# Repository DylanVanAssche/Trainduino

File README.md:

ReadMe Trainduino
=================

Trainduino is a project that combines the power of the Arduino with the beautifull modeltrains. 
The electronics that are avaibale in the modeltrain world are overpriced for the limited functions they have, 
so this is your alternative!

RandomLEDController
-------------------

Controls a day/night process on my modelroad. It works with a cylcus of 24 minutes. 
Every minute counts the Arduino as one 'hour'.After the whole cyclus, the Arduino resets the timer.
The RandomLEDController can control 14 LED's in houses and has also 1 output for the streetlights.

RGBLEDController
----------------

Does the same as the RandomLEDController but this time it controls a RGB LEDstrip and a white LEDstrip to simulate a 
completely day/night. It runs synchrone with the RandomLEDController because it use the same timer system.

DCCSwitchController
-------------------

DCC accessory decoder with some extra nice functions. You can control 2 switches and 1 brake module.
There are also 4 outputs for a signal. The 3 LED's on the board show the status of the incomming commands.

S88Wireless
-----------

The S88Wireless system give you the possibilities to use your cheap S88 bus over a wireless connection. 
It's perfectly for a railroad track that has to be flexible and portable since you don't need the 6pin ribbon cable all around your layout!

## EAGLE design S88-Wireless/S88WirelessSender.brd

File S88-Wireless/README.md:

S88Wireless
-----------

The S88Wireless system is an Arduino based S88 feedback unit that transfers his data over a Wireless 2.4 Ghz connection.
The radio that we used for the S88Wireless is a cheap NRF24L01+ unit.

The BASE sketch collects all the information from the slave with a polling request and sends out the data on the S88 bus of your command station. The BASE sketch also monitors the data and checks if the slaves are alive. If not, the BASE sketch will trigger an emergency stop on your command station by using the short circuit detection from the DCC booster bus.

The SLAVE sketch monitors 8 pins and reports the status back to the base when the slave have been polled by the base.

The EAGLE PCB's are also available in this repository.

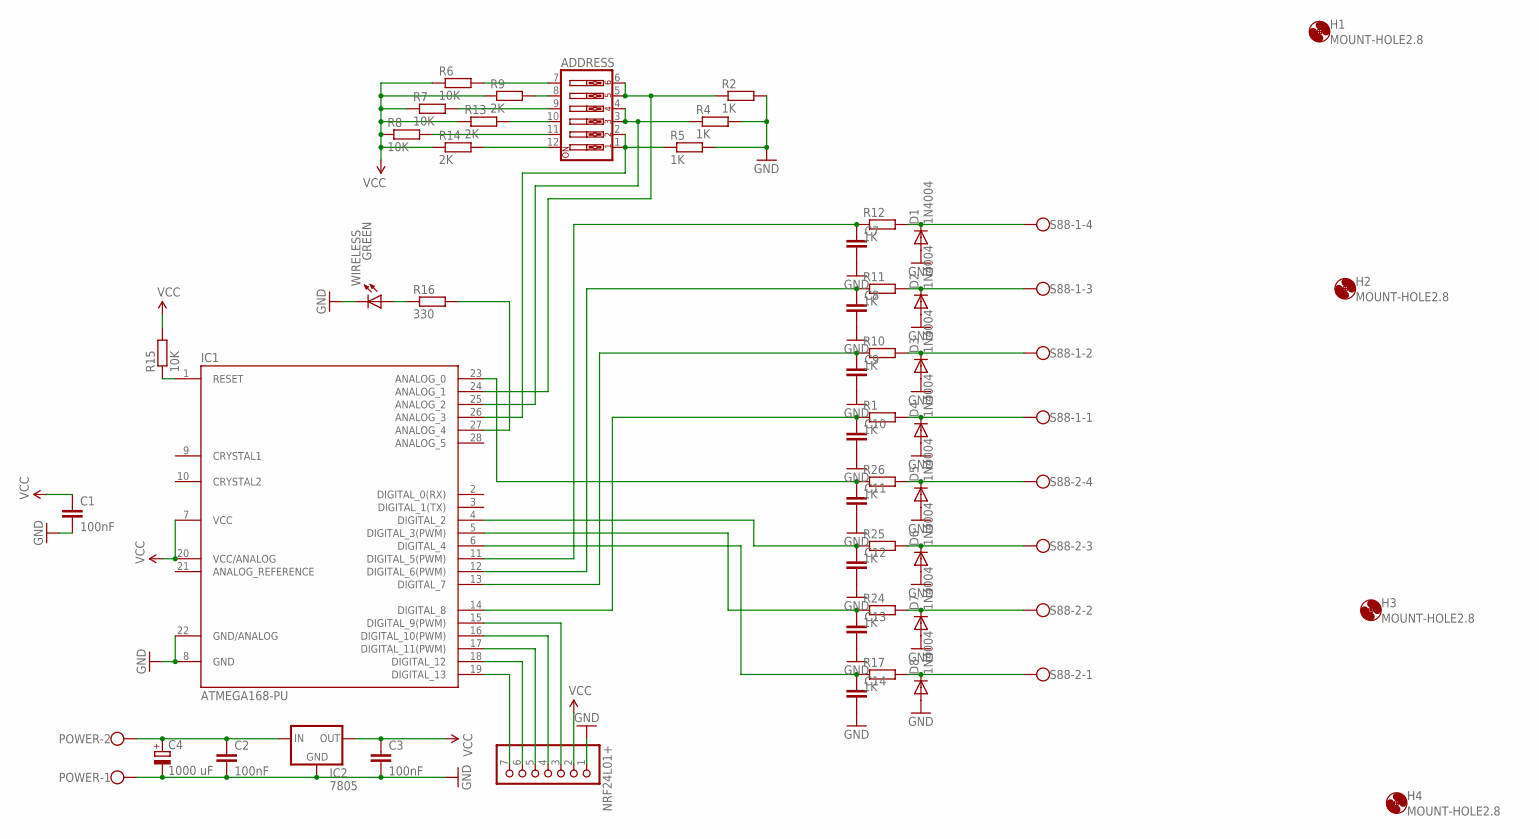
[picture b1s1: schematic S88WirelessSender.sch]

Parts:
ADDRESS: SW_DIP-6; EDG-06
C1, C2, C3: 100nF; C025-030X050
C4: 1000 uF; E5-13
C7, C8, C9, C10, C11, C12, C13, C14: C-EU025-024X044; C025-024X044
D1, D2, D3, D4, D5, D6, D7, D8: 1N4004; DO41-10
H1, H2, H3, H4: MOUNT-HOLE2.8; 2,8
IC1: ATMEGA168-PU; DIL28-3
IC2: 7805; 78XXS
NRF24L01+: PINHD-1X7; 1X07
POWER: W237-102
R1, R2, R4, R5, R10, R11, R12, R17, R24, R25, R26: 1K; 0204/7
R6, R7, R8, R15: 10K; 0204V
R9, R13, R14: 2K; 0204V
R16: 330; 0204V
S88-1, S88-2: W237-4
WIRELESS: GREEN; LED3MM

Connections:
GND: C1.2, C2.2, C3.2, C4.-, C7.2, C8.2, C9.2, C10.2, C11.2, C12.2, C13.2, C14.2, D1.A, D2.A, D3.A, D4.A, D5.A, D6.A, D7.A, D8.A, IC1.8 (GND), IC1.22 (GND/ANALOG), IC2.GND, NRF24L01+.1, POWER.1, R2.2, R4.2, R5.2, WIRELESS.K (C)
unnamed: IC1.16 (DIGITAL_10(PWM)), NRF24L01+.4
unnamed: IC1.15 (DIGITAL_9(PWM)), NRF24L01+.3
unnamed: IC1.19 (DIGITAL_13), NRF24L01+.7
unnamed: IC1.17 (DIGITAL_11(PWM)), NRF24L01+.5
unnamed: IC1.18 (DIGITAL_12), NRF24L01+.6
unnamed: D2.C, R11.2, S88-1.3
unnamed: D4.C, R1.2, S88-1.1
unnamed: D5.C, R26.2, S88-2.4
unnamed: D6.C, R25.2, S88-2.3
unnamed: D7.C, R24.2, S88-2.2
unnamed: ADDRESS.11, R8.2
unnamed: ADDRESS.9, R7.2
unnamed: ADDRESS.7, R6.2
unnamed: ADDRESS.8, R9.2
unnamed: D8.C, R17.2, S88-2.1
unnamed: C12.1, IC1.4 (DIGITAL_2), R25.1
unnamed: IC1.27 (ANALOG_4), R16.2
unnamed: ADDRESS.10, R13.2
unnamed: ADDRESS.12, R14.2
unnamed: ADDRESS.1, ADDRESS.2, IC1.26 (ANALOG_3), R5.1
unnamed: ADDRESS.3, ADDRESS.4, IC1.25 (ANALOG_2), R4.1
unnamed: C7.1, IC1.11 (DIGITAL_5(PWM)), R12.1
unnamed: C8.1, IC1.12 (DIGITAL_6(PWM)), R11.1
unnamed: C9.1, IC1.13 (DIGITAL_7), R10.1
unnamed: R16.1, WIRELESS.A
unnamed: C10.1, IC1.14 (DIGITAL_8), R1.1
unnamed: ADDRESS.5, ADDRESS.6, IC1.24 (ANALOG_1), R2.1
unnamed: C11.1, IC1.23 (ANALOG_0), R26.1
unnamed: D1.C, R12.2, S88-1.4
unnamed: C13.1, IC1.5 (DIGITAL_3(PWM)), R24.1
unnamed: IC1.1 (RESET), R15.1
unnamed: C14.1, IC1.6 (DIGITAL_4), R17.1
unnamed: D3.C, R10.2, S88-1.2
unnamed: C2.1, C4.+, IC2.IN, POWER.2
VCC: C1.1, C3.1, IC1.7 (VCC), IC1.20 (VCC/ANALOG), IC2.OUT, NRF24L01+.2, R6.1, R7.1, R8.1, R9.1, R13.1, R14.1, R15.2

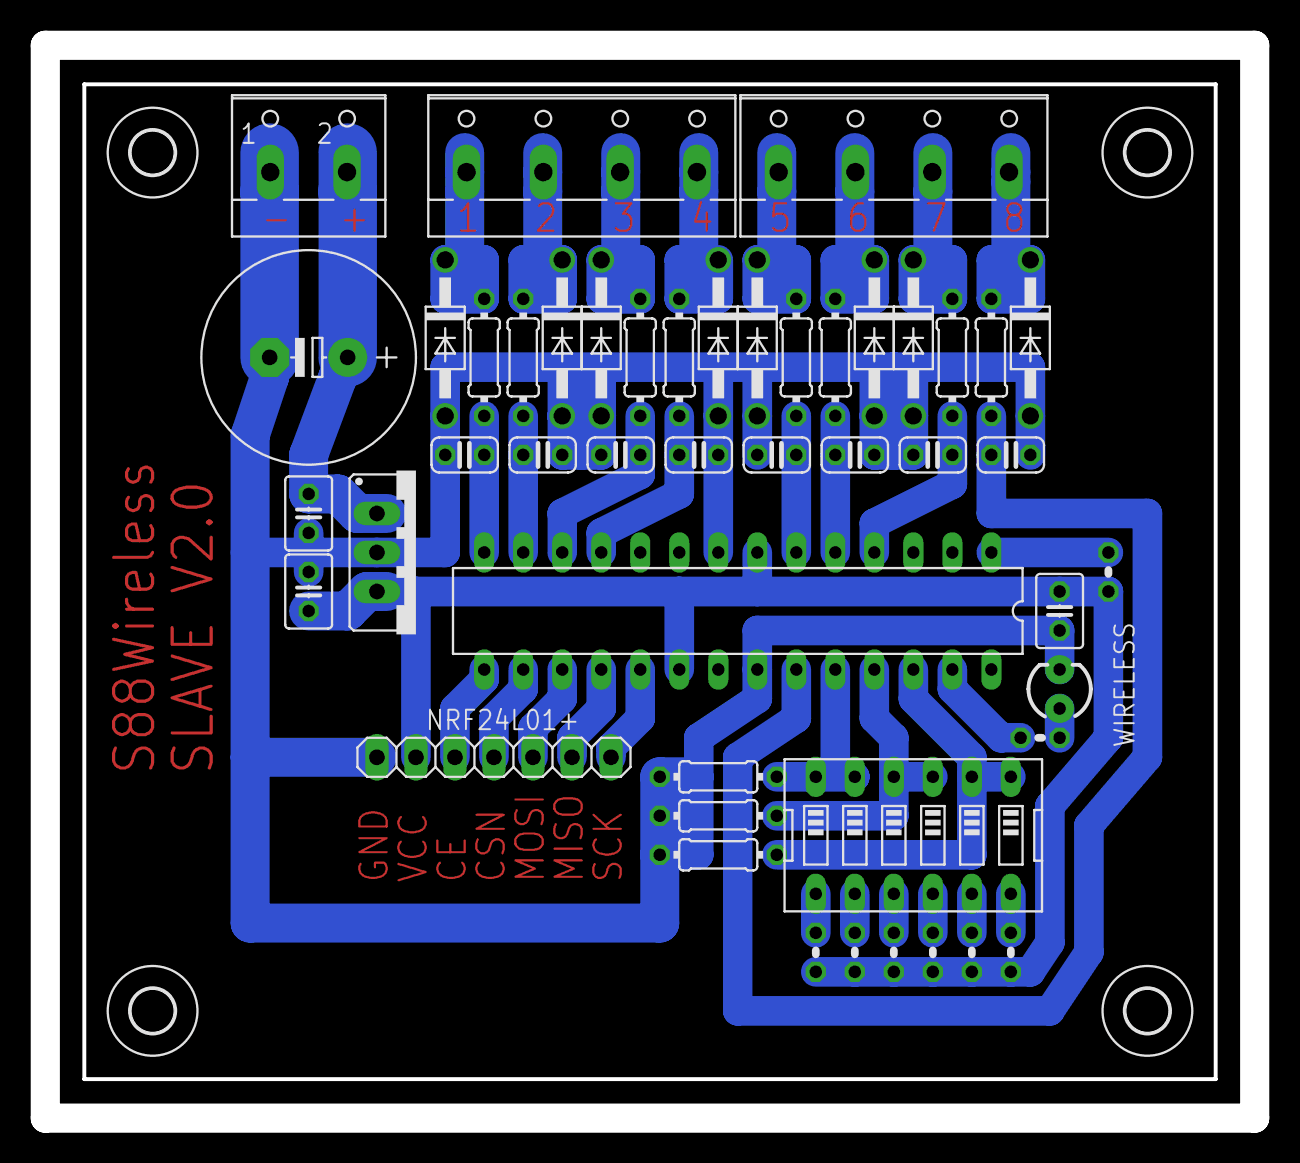
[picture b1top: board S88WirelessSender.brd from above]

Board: 2 copper layers, 78.7 x 69.8 mm, 51 parts (0 on the bottom side), 36 nets.

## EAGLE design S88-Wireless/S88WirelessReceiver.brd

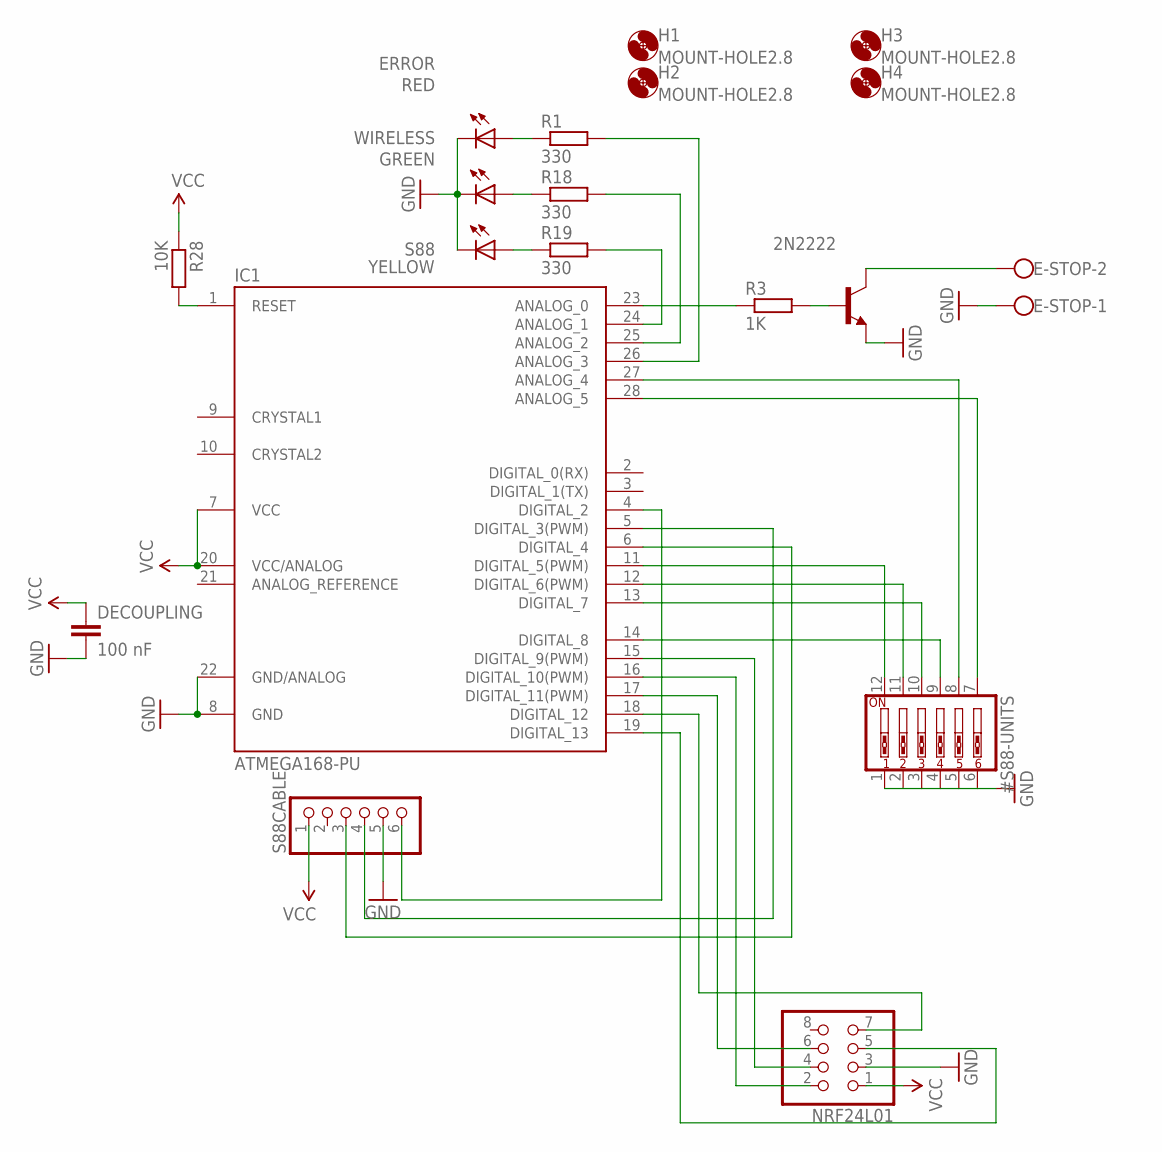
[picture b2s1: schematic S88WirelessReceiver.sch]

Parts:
2N2222: -NPN-TO92-EBC; TO92-EBC
#S88-UNITS: SW_DIP-6; EDG-06
DECOUPLING: 100 nF; C025-024X044
E-STOP: W237-102
ERROR: RED; LED3MM
H1, H2, H3, H4: MOUNT-HOLE2.8; 2,8
IC1: ATMEGA168-PU; DIL28-3
NRF24L01: PINHD-2X4; 2X04
R1, R18, R19: 330; 0204/7
R3: 1K; 0204V
R28: 10K; 0204/7
S88: YELLOW; LED3MM
S88CABLE: PINHD-1X6; 1X06
WIRELESS: GREEN; LED3MM

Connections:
GND: 2N2222.E, #S88-UNITS.1, #S88-UNITS.2, #S88-UNITS.3, #S88-UNITS.4, #S88-UNITS.5, #S88-UNITS.6, DECOUPLING.2, E-STOP.1, ERROR.K (C), IC1.8 (GND), IC1.22 (GND/ANALOG), NRF24L01.3, S88.K (C), S88CABLE.5, WIRELESS.K (C)
unnamed: IC1.4 (DIGITAL_2), S88CABLE.6
unnamed: IC1.16 (DIGITAL_10(PWM)), NRF24L01.2
unnamed: IC1.15 (DIGITAL_9(PWM)), NRF24L01.4
unnamed: IC1.19 (DIGITAL_13), NRF24L01.5
unnamed: IC1.17 (DIGITAL_11(PWM)), NRF24L01.6
unnamed: IC1.18 (DIGITAL_12), NRF24L01.7
unnamed: IC1.5 (DIGITAL_3(PWM)), S88CABLE.4
unnamed: IC1.6 (DIGITAL_4), S88CABLE.3
unnamed: #S88-UNITS.12, IC1.11 (DIGITAL_5(PWM))
unnamed: #S88-UNITS.11, IC1.12 (DIGITAL_6(PWM))
unnamed: #S88-UNITS.10, IC1.13 (DIGITAL_7)
unnamed: #S88-UNITS.9, IC1.14 (DIGITAL_8)
unnamed: #S88-UNITS.7, IC1.28 (ANALOG_5)
unnamed: #S88-UNITS.8, IC1.27 (ANALOG_4)
unnamed: 2N2222.B, R3.2
unnamed: ERROR.A, R1.1
unnamed: IC1.26 (ANALOG_3), R1.2
unnamed: IC1.23 (ANALOG_0), R3.1
unnamed: 2N2222.C, E-STOP.2
unnamed: IC1.25 (ANALOG_2), R18.2
unnamed: R18.1, WIRELESS.A
unnamed: R19.1, S88.A
unnamed: IC1.1 (RESET), R28.2
unnamed: IC1.24 (ANALOG_1), R19.2
VCC: DECOUPLING.1, IC1.7 (VCC), IC1.20 (VCC/ANALOG), NRF24L01.1, R28.1, S88CABLE.1

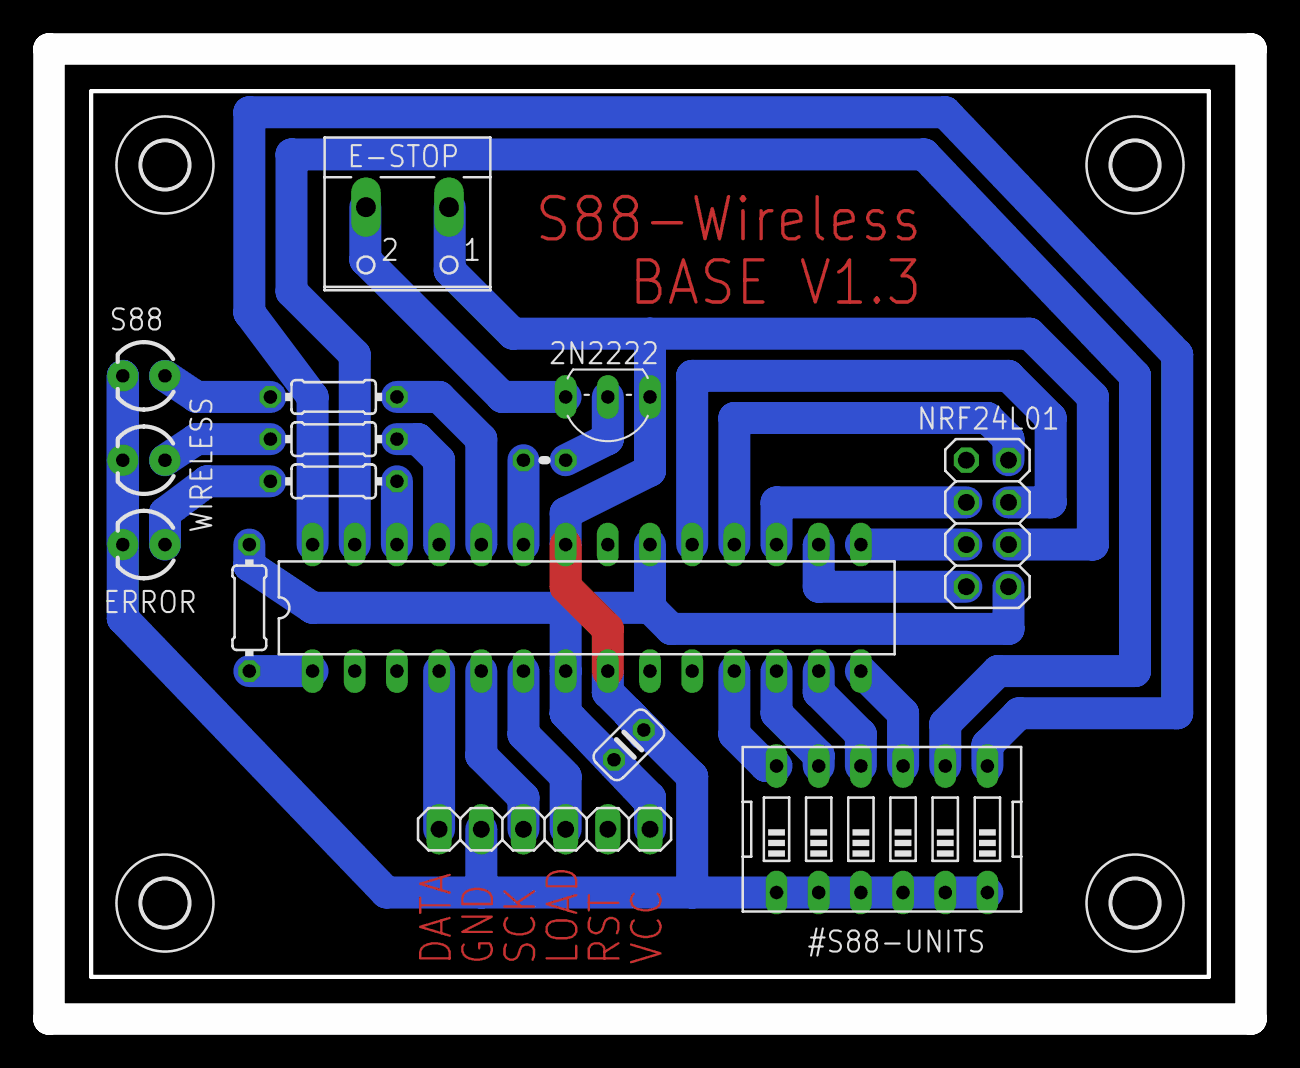
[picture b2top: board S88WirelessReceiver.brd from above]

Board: 2 copper layers, 72.4 x 58.4 mm, 19 parts (0 on the bottom side), 26 nets.

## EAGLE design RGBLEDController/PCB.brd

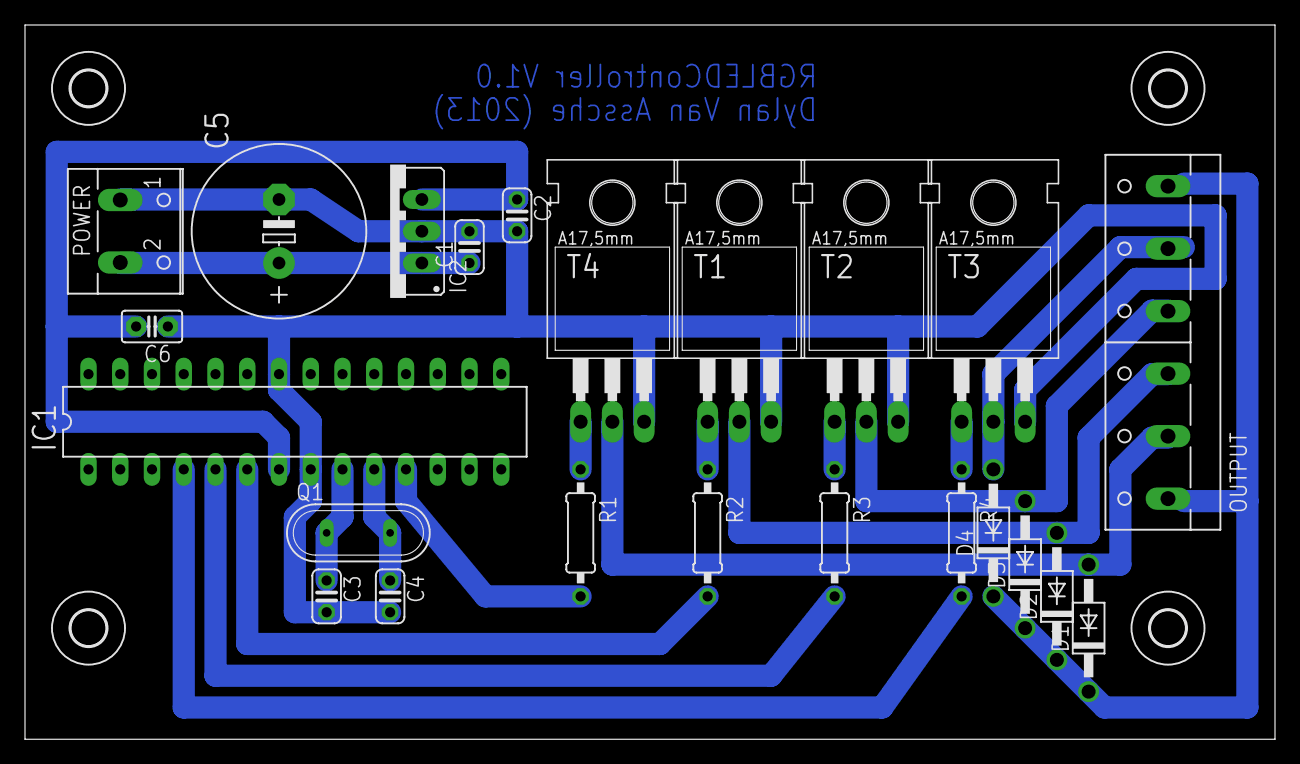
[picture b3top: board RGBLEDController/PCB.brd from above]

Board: 2 copper layers, 100.0 x 57.1 mm, 27 parts (0 on the bottom side), 17 nets.

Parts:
C1, C2, C3, C4: C025-024X044
C5: 1000 uF; E5-13
C6: C2.5-2
D1, D2, D3, D4: 1N4004; DO41-10
H1, H2, H3, H4: MOUNT-HOLE2.8; 2,8
IC1: ATMEGA168-PU; DIL28-3
IC2: 78XXS
OUTPUT: W237-136
POWER: W237-102
Q1: QS
R1, R2, R3, R4: 1K; 0207/10
T1, T2, T3, T4: TIP122; TO220

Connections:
GND: C1.2, C2.2, C3.2, C4.2, C5.-, C6.1, IC1.8, IC1.22, IC2.GND, POWER.1, T1.3, T2.3, T3.3, T4.3
unnamed: C1.1, C5.+, D1.C, D2.C, D3.C, D4.C, IC2.IN, OUTPUT.1, OUTPUT.6, POWER.2
unnamed: R4.1, T3.1
unnamed: D4.A, OUTPUT.5, T3.2
unnamed: C4.1, IC1.10, Q1.2
unnamed: C3.1, IC1.9, Q1.1
unnamed: D3.A, OUTPUT.4, T2.2
unnamed: D2.A, OUTPUT.3, T1.2
unnamed: D1.A, OUTPUT.2, T4.2
unnamed: R3.1, T2.1
unnamed: R2.1, T1.1
unnamed: R1.1, T4.1
unnamed: IC1.4, R4.2
unnamed: IC1.5, R3.2
unnamed: IC1.6, R2.2
unnamed: IC1.11, R1.2
VCC: C2.1, C6.2, IC1.7, IC1.20, IC2.OUT

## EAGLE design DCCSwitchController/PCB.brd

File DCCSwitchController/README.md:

DCCSwitchController
-------------------

DCC accessory decoder with some extra nice functions. You can control 2 switches and 1 brake module. 
There's also 4 outputs for a signal. The 3 LED's on the board show the status of the incomming commands.

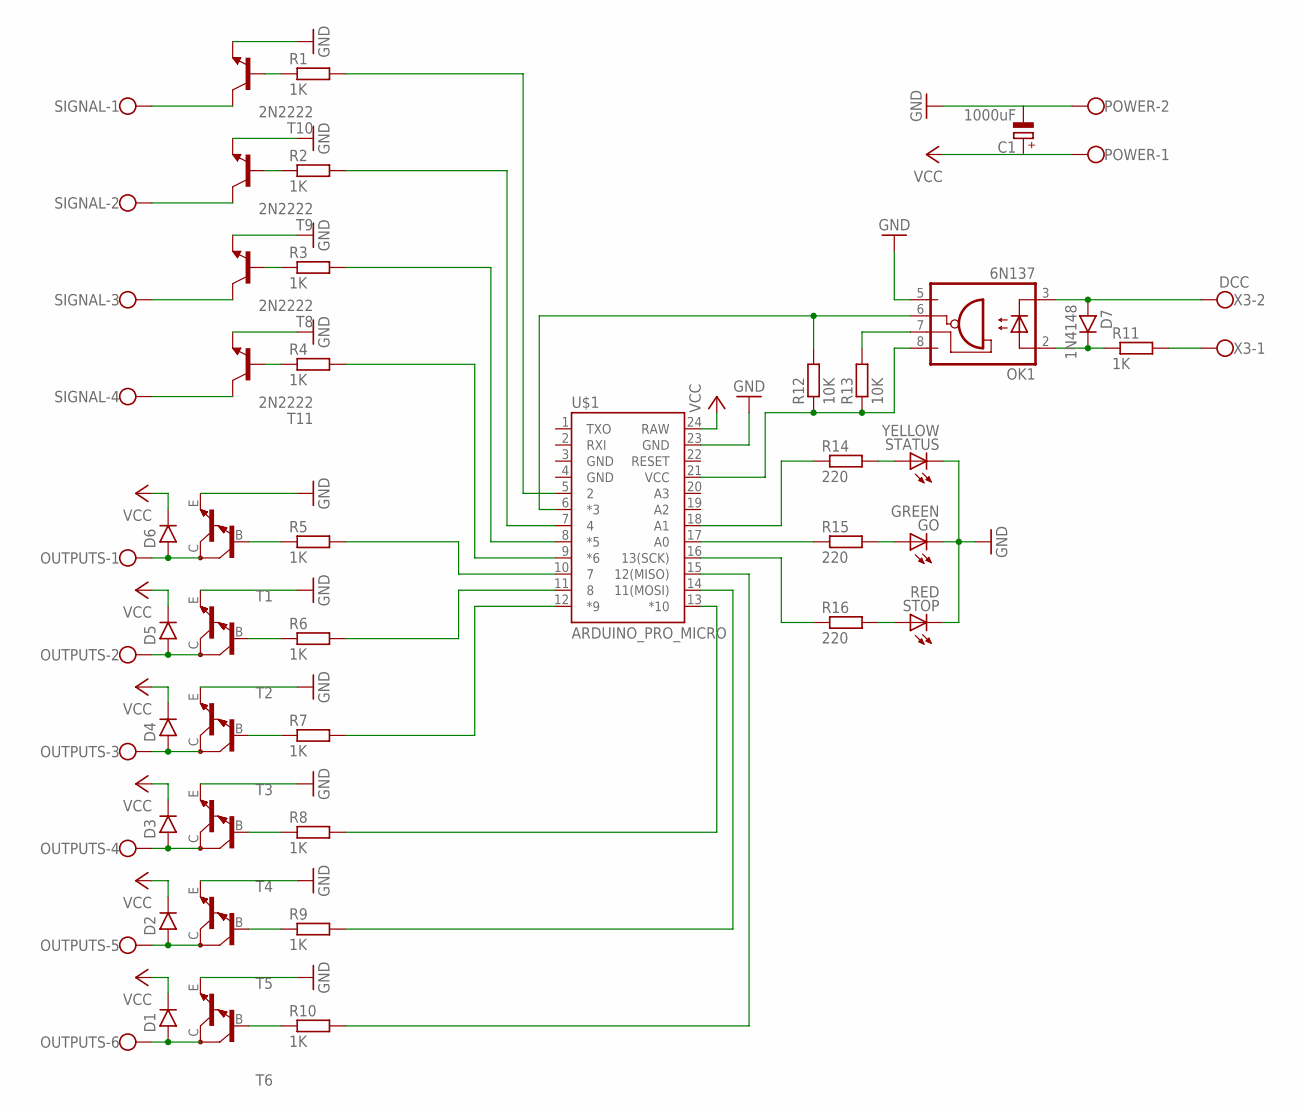
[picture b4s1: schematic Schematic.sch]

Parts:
C1: 1000uF; E5-13
D1, D2, D3, D4, D5, D6: DO41.3; DO41-3
D7: 1N4148; DO35-3
GO: GREEN; LED3MM
OK1: 6N137; DIL08
OUTPUTS: W237-6
POWER: W237-102
R1, R2, R3, R4, R5, R6, R7, R8, R9, R10, R11: 1K; 0204/7
R12, R13: 10K; 0204/7
R14, R15, R16: 220; 0204/7
SIGNAL: W237-4
STATUS: YELLOW; LED3MM
STOP: RED; LED3MM
T1, T2, T3, T4, T5, T6: TIP122VERTICAL; TO220AV
T8, T9, T10, T11: 2N2222; TO92-EBC
U$1: ARDUINO_PRO_MICRO
X3: DCC; W237-102

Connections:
GND: C1.-, GO.K (C), OK1.5 (GND), POWER.2, STATUS.K (C), STOP.K (C), T1.E, T2.E, T3.E, T4.E, T5.E, T6.E, T8.E, T9.E, T10.E, T11.E, U$1.23 (GND)
unnamed: R4.1, T11.B
unnamed: R3.1, T8.B
unnamed: R2.1, T9.B
unnamed: R1.1, T10.B
unnamed: SIGNAL.1, T10.C
unnamed: SIGNAL.2, T9.C
unnamed: SIGNAL.3, T8.C
unnamed: SIGNAL.4, T11.C
unnamed: D1.A, OUTPUTS.6, T6.C
unnamed: D2.A, OUTPUTS.5, T5.C
unnamed: D3.A, OUTPUTS.4, T4.C
unnamed: D4.A, OUTPUTS.3, T3.C
unnamed: D5.A, OUTPUTS.2, T2.C
unnamed: D6.A, OUTPUTS.1, T1.C
unnamed: R5.1, T1.B
unnamed: R6.1, T2.B
unnamed: R7.1, T3.B
unnamed: R8.1, T4.B
unnamed: R9.1, T5.B
unnamed: R10.1, T6.B
unnamed: OK1.6 (VO), R12.2, U$1.6 (*3)
unnamed: R1.2, U$1.5 (2)
unnamed: R2.2, U$1.7 (4)
unnamed: R3.2, U$1.8 (*5)
unnamed: R4.2, U$1.9 (*6)
unnamed: R5.2, U$1.10 (7)
unnamed: R6.2, U$1.11 (8)
unnamed: R7.2, U$1.12 (*9)
unnamed: R8.2, U$1.13 (*10)
unnamed: R9.2, U$1.14 (11(MOSI))
unnamed: R10.2, U$1.15 (12(MISO))
unnamed: D7.C, OK1.2 (A), R11.1
unnamed: D7.A, OK1.3 (C), X3.2
unnamed: R11.2, X3.1
unnamed: OK1.7 (VE), R13.2
unnamed: OK1.8 (VCC), R12.1, R13.1, U$1.21 (VCC)
unnamed: R14.2, STATUS.A
unnamed: GO.A, R15.2
unnamed: R16.2, STOP.A
unnamed: R16.1, U$1.16 (13(SCK))
unnamed: R15.1, U$1.17 (A0)
unnamed: R14.1, U$1.18 (A1)
VCC: C1.+, D1.C, D2.C, D3.C, D4.C, D5.C, D6.C, POWER.1, U$1.24 (RAW)

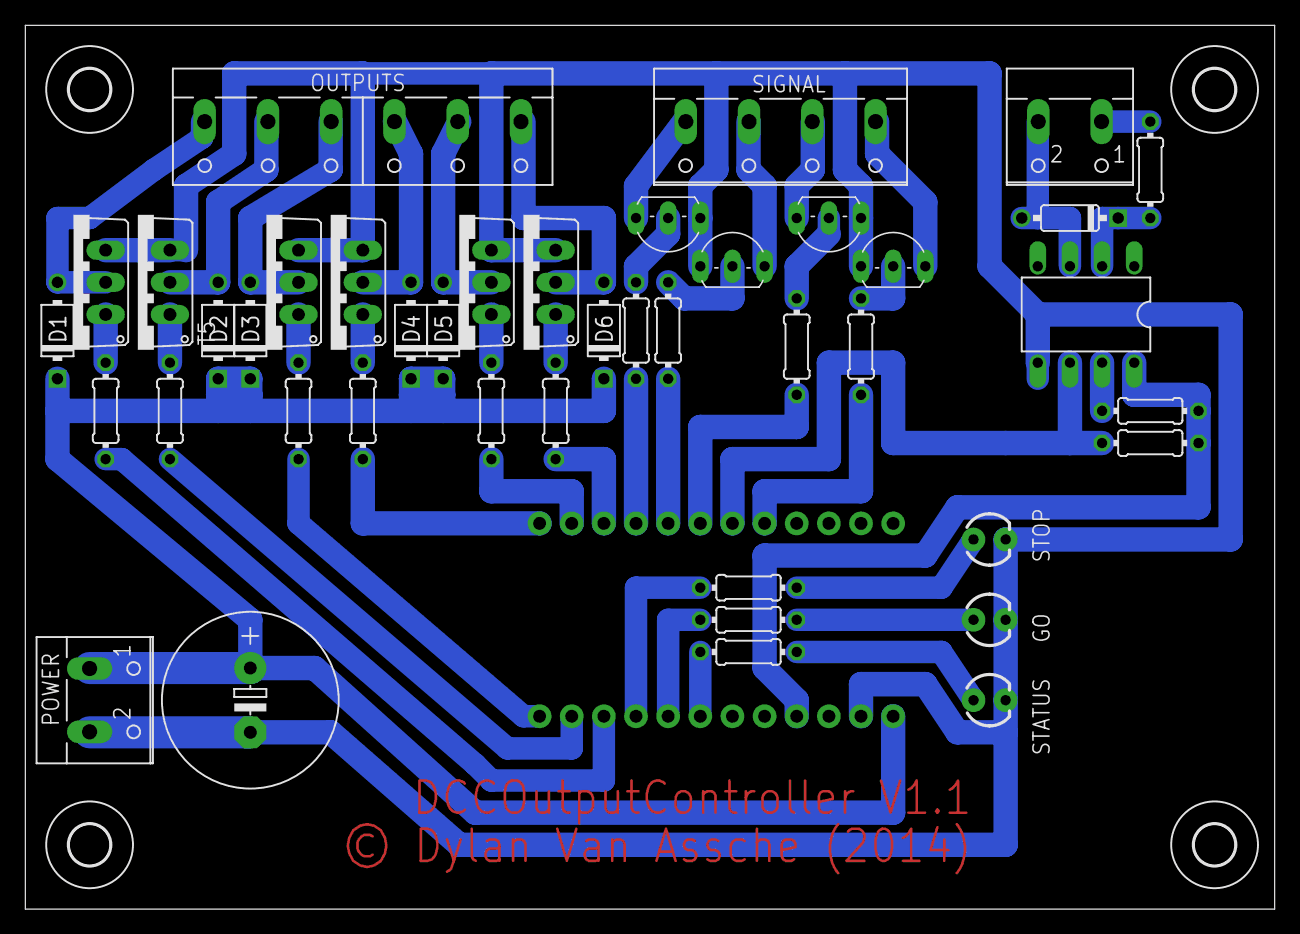
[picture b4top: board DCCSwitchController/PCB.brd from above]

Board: 2 copper layers, 98.7 x 69.8 mm, 47 parts (0 on the bottom side), 44 nets.

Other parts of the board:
U$2, U$3, U$4, U$5: 3,2

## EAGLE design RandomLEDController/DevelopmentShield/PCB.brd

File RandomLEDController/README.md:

RandomLEDController
===================

Controls a day/night process on my modelroad. It works with a cylcus of 24 minutes. 
Every minute counts the Arduino as one 'hour'. After the whole cyclus, the Arduino resets the timer.
The RandomLEDController can control 14 LED's in houses and has also 1 output for the streetlights.

29 - 12 - 2013
--------------

First prerelease version of the RandomLEDController (V0.9) is online! 

04 - 01 - 2014
--------------

FULL release of the RandomLEDController (V1.0) is now available!

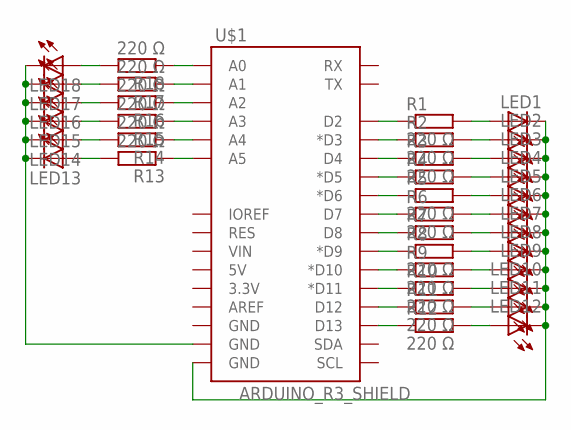
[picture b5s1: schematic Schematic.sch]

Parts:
LED1, LED2, LED3, LED4, LED5, LED6, LED7, LED8, LED9, LED10, LED11, LED12, LED13, LED14, LED15, LED16, LED17, LED18: LED3MM
R1, R2, R3, R5, R6, R8, R9, R10, R11, R12, R13, R14, R15, R16, R17, R18: 220 Ω; 0204/7
R4, R7: R-EU_0204/7; 0204/7
U$1: ARDUINO_R3_SHIELD; UNO_R3_SHIELD

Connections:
unnamed: R12.1, U$1.D13
unnamed: R11.1, U$1.D12
unnamed: R10.1, U$1.D11 (*D11)
unnamed: R9.1, U$1.D10 (*D10)
unnamed: R8.1, U$1.D9 (*D9)
unnamed: R7.1, U$1.D8
unnamed: R6.1, U$1.D7
unnamed: R5.1, U$1.D6 (*D6)
unnamed: R4.1, U$1.D5 (*D5)
unnamed: R3.1, U$1.D4
unnamed: R2.1, U$1.D3 (*D3)
unnamed: R1.1, U$1.D2
unnamed: LED1.A, R1.2
unnamed: LED2.A, R2.2
unnamed: LED3.A, R3.2
unnamed: LED4.A, R4.2
unnamed: LED5.A, R5.2
unnamed: LED6.A, R6.2
unnamed: LED7.A, R7.2
unnamed: LED8.A, R8.2
unnamed: LED9.A, R9.2
unnamed: LED10.A, R10.2
unnamed: LED11.A, R11.2
unnamed: LED12.A, R12.2
unnamed: LED1.K (C), LED2.K (C), LED3.K (C), LED4.K (C), LED5.K (C), LED6.K (C), LED7.K (C), LED8.K (C), LED9.K (C), LED10.K (C), LED11.K (C), LED12.K (C), U$1.GND@0 (GND)
unnamed: LED13.A, R13.2
unnamed: LED14.A, R14.2
unnamed: LED15.A, R15.2
unnamed: LED16.A, R16.2
unnamed: LED17.A, R17.2
unnamed: LED13.K (C), LED14.K (C), LED15.K (C), LED16.K (C), LED17.K (C), LED18.K (C), U$1.GND@1 (GND)
unnamed: R13.1, U$1.A5
unnamed: R15.1, U$1.A3
unnamed: R16.1, U$1.A2
unnamed: R17.1, U$1.A1
unnamed: R14.1, U$1.A4
unnamed: LED18.A, R18.2
unnamed: R18.1, U$1.A0

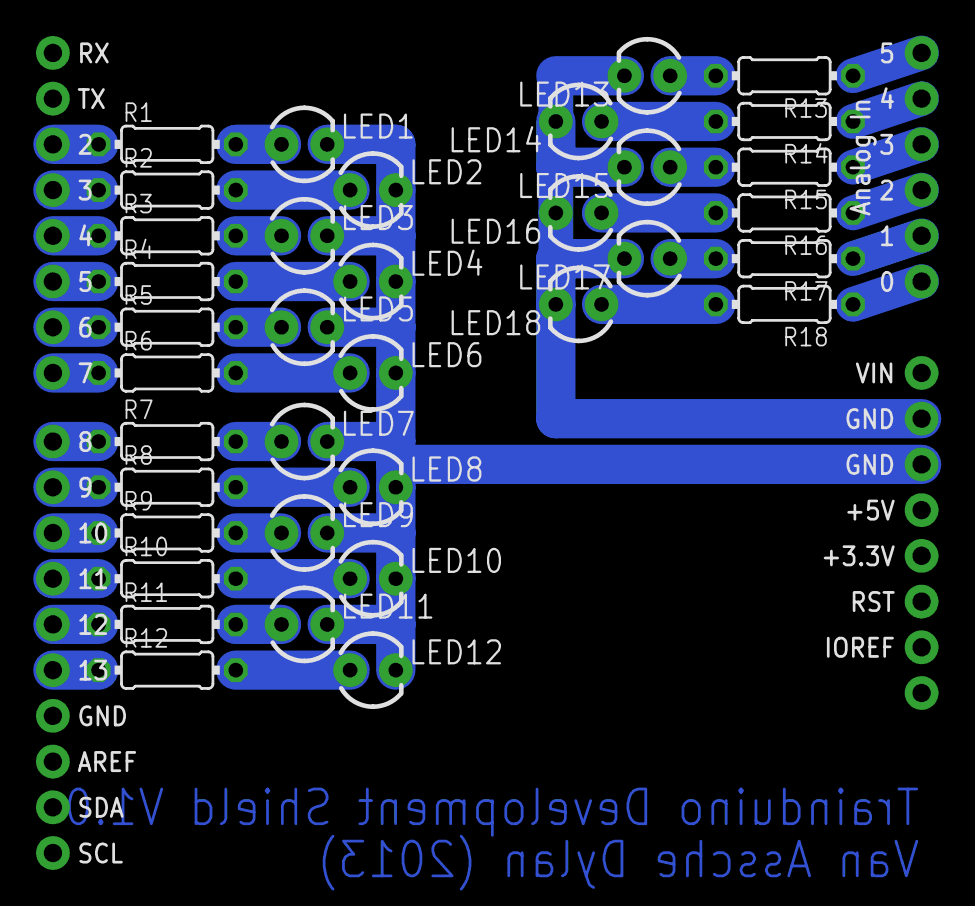
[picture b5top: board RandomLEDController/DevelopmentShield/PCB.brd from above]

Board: 2 copper layers, 37 parts (0 on the bottom side), 38 nets.

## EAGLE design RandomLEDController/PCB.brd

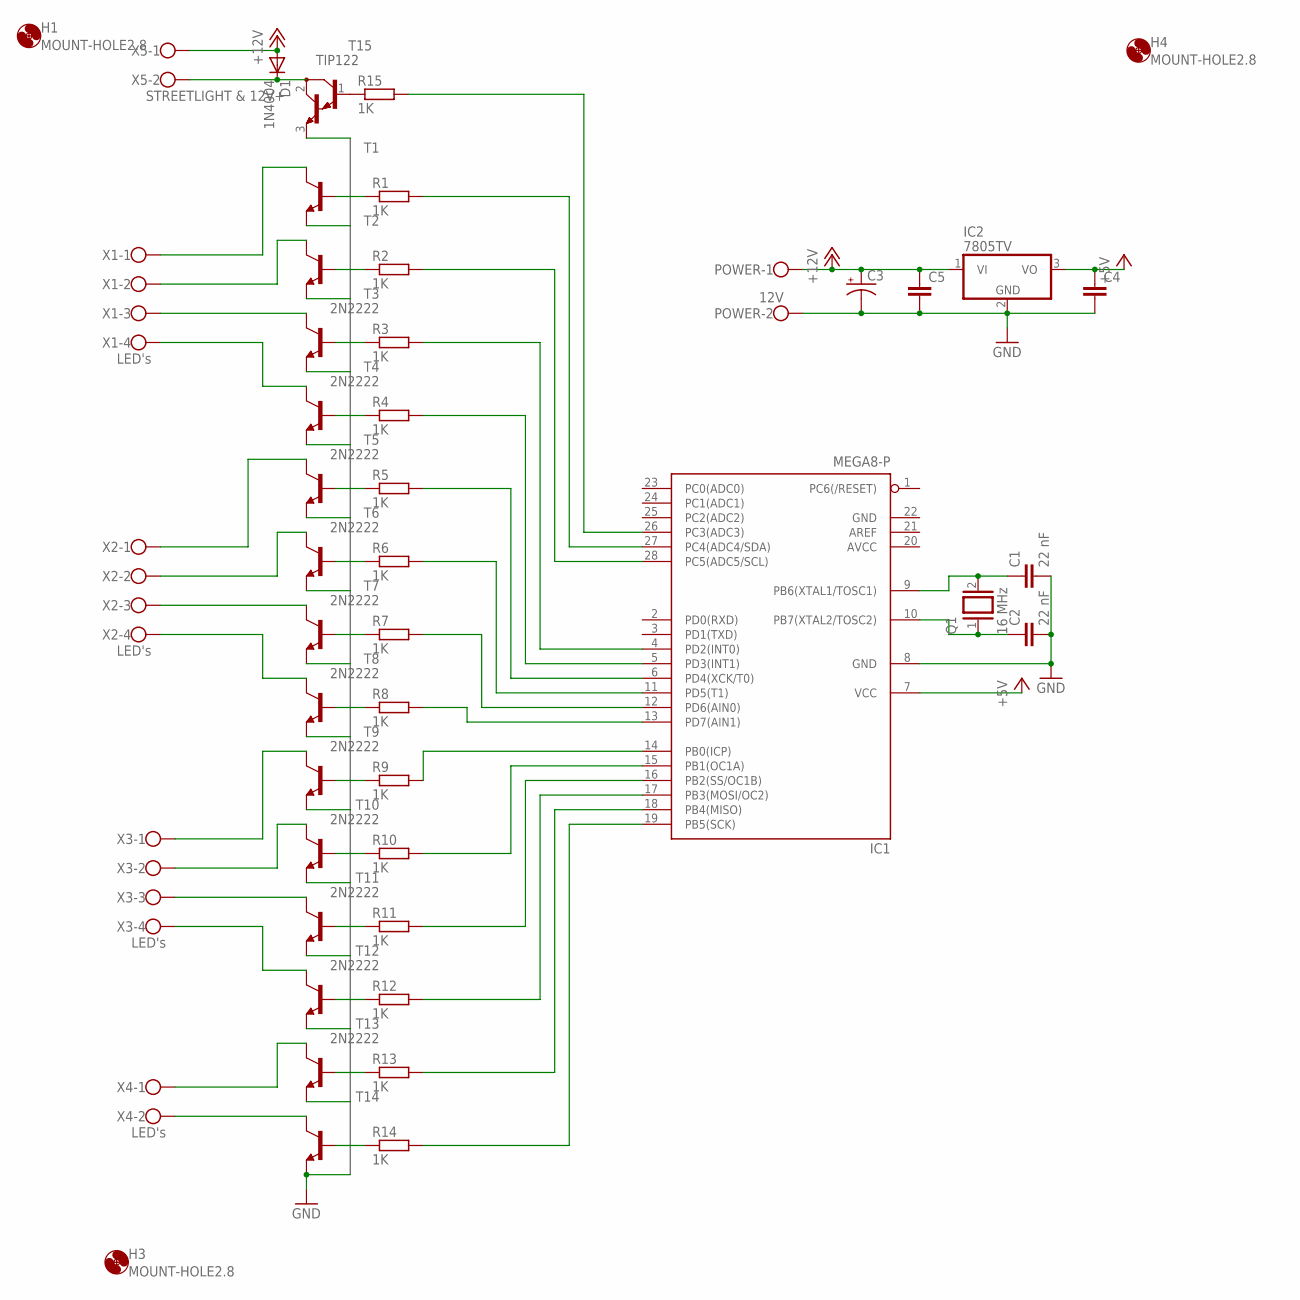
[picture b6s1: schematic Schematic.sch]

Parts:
C1, C2: 22 nF; C2.5-2
C3: CPOL-USE5-13; E5-13
C4, C5: C2.5/2; C2.5-2
D1: 1N4004; DO41-10
H1, H3, H4: MOUNT-HOLE2.8; 2,8
IC1: MEGA8-P; DIL28-3
IC2: 7805TV; TO220V
POWER: 12V; W237-102
Q1: 16 MHz; QS
R1, R2, R3, R4, R5, R6, R7, R8, R9, R10, R11, R12, R13, R14, R15: 1K; 0207/10
T1, T2, T14: -NPN-TO92-EBC; TO92-EBC
T3, T4, T5, T6, T7, T8, T9, T10, T11, T12, T13: 2N2222; TO92-EBC
T15: TIP122; TO220
X1, X2, X3: LED's; W237-4
X4: LED's; W237-102
X5: STREETLIGHT & 12V+; W237-102

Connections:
+5V: C4.1, IC1.7 (VCC), IC2.3 (VO)
+12V: C3.+, C5.1, D1.A, IC2.1 (VI), POWER.1, X5.1
AVCC: IC1.20 (AVCC)
GND: C1.2, C2.2, C3.-, C4.2, C5.2, IC1.8 (GND), IC1.22 (GND), IC2.2 (GND), POWER.2, T1.E, T2.E, T3.E, T4.E, T5.E, T6.E, T7.E, T8.E, T9.E, T10.E, T11.E, T12.E, T13.E, T14.E, T15.3 (E)
unnamed: R9.1, T9.B
unnamed: R10.1, T10.B
unnamed: R11.1, T11.B
unnamed: R12.1, T12.B
unnamed: R13.1, T13.B
unnamed: R14.1, T14.B
unnamed: R6.1, T6.B
unnamed: R5.1, T5.B
unnamed: R7.1, T7.B
unnamed: R8.1, T8.B
unnamed: R4.1, T4.B
unnamed: R3.1, T3.B
unnamed: R2.1, T2.B
unnamed: R1.1, T1.B
unnamed: T7.C, X2.3
unnamed: T3.C, X1.3
unnamed: T5.C, X2.1
unnamed: T8.C, X2.4
unnamed: T9.C, X3.1
unnamed: T10.C, X3.2
unnamed: T11.C, X3.3
unnamed: T12.C, X3.4
unnamed: T13.C, X4.1
unnamed: T14.C, X4.2
unnamed: IC1.19 (PB5(SCK)), R14.2
unnamed: IC1.18 (PB4(MISO)), R13.2
unnamed: IC1.17 (PB3(MOSI/OC2)), R12.2
unnamed: IC1.16 (PB2(SS/OC1B)), R11.2
unnamed: IC1.15 (PB1(OC1A)), R10.2
unnamed: IC1.14 (PB0(ICP)), R9.2
unnamed: IC1.27 (PC4(ADC4/SDA)), R1.2
unnamed: IC1.28 (PC5(ADC5/SCL)), R2.2
unnamed: IC1.4 (PD2(INT0)), R3.2
unnamed: IC1.5 (PD3(INT1)), R4.2
unnamed: IC1.6 (PD4(XCK/T0)), R5.2
unnamed: IC1.11 (PD5(T1)), R6.2
unnamed: IC1.12 (PD6(AIN0)), R7.2
unnamed: IC1.13 (PD7(AIN1)), R8.2
unnamed: R15.1, T15.1 (B)
unnamed: C1.1, IC1.9 (PB6(XTAL1/TOSC1)), Q1.2
unnamed: C2.1, IC1.10 (PB7(XTAL2/TOSC2)), Q1.1
unnamed: T6.C, X2.2
unnamed: T4.C, X1.4
unnamed: D1.C, T15.2 (C), X5.2
unnamed: T1.C, X1.1
unnamed: T2.C, X1.2
unnamed: IC1.26 (PC3(ADC3)), R15.2

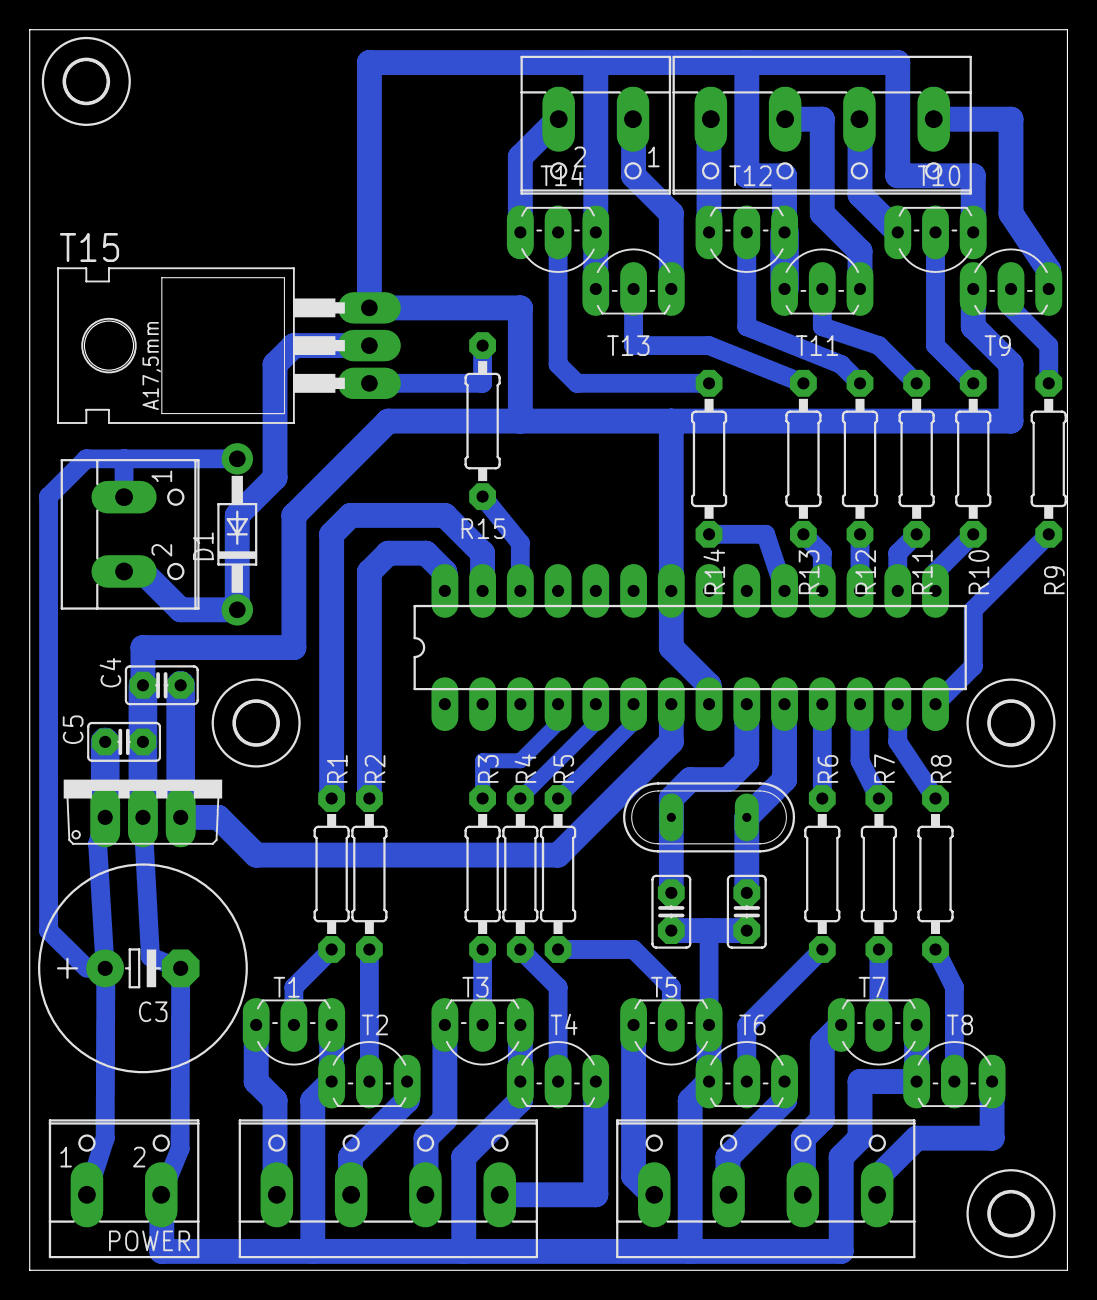
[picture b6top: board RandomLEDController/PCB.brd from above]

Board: 2 copper layers, 69.8 x 83.5 mm, 49 parts (0 on the bottom side), 50 nets.

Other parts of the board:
H2: MOUNT-HOLE2.8; 2,8

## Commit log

2013-11-23 README.md V1.0
2013-12-21 EAGLE Schematic
2013-12-21 EAGLE PCB RandomLEDController
2013-12-21 Eagle schematic RandomLEDController
2013-12-21 Update V1.1
    Bugfix: 7805 voltage regulator wiring
2013-12-21 Update V1.1
    Bugfix: 7805 voltage regulator wiring.
2013-12-25 DevelopmentShield RandomLEDController V1.0
    PCB EAGLE DevelopmentShield RandomLEDController V1.0
2013-12-25 Schematic Development Shield RGBLEDController V1.0
    EAGLE Schematic Development Shield RGBLEDController V1.0
2013-12-29 RandomLEDController Arduino Sketch V1.0 PRERELEASE
    RandomLEDController Arduino Sketch V1.0 PRERELEASE
    This is a prerelease! This version isn't completely tested.
    A stable & fully tested release is coming soon.
2013-12-29 PRERELEASE V0.9
    Arduino sketch of the RandomLEDController (PRERELEASE)
    This version isn't completely tested yet! You can use this sketch at your own risk (the same for the rest of other files from Trainduino).
2013-12-29 PRERELEASE V0.9
2013-12-30 PRERELEASE V0.9.1
2014-01-05 RELEASE V1.0
2014-01-05 Update 04 - 01 - 2014
2014-02-02 Release V1.0
    RGBLEDController release V1.0
2014-02-02 Schematic V1.1
2014-02-02 PCB V1.1
2014-02-14 V1.0 RELEASE
    Version 1.0 RELEASE DCCSwitchController.
2014-02-14 V1.0 RELEASE
2014-02-14 V1.2
2014-06-16 RandomLEDController V1.3
    A LOT NEW FEATURES! Check it out!
2014-06-16 RGBLEDController V1.2
    A LOT NEW FEATURES! Check it out!
2014-08-20 Arduino S88 that can simulate up to 32 S88 units
2014-08-20 MEGA-S88 is an Arduino based S88 unit.
    This S88 unit can replace up to 32 S88 units.
2014-08-20 V1.0 RELEASE
    S88 feedback over a wireless connection
2014-08-20 V1.0 RELEASE
    This sketch is the slave for the S88 Wireless Trainduino system.
2014-08-20 S88Wireless ADDED
2014-08-20 MEGA-S88 README
2014-08-20 Added title
2014-08-20 S88Wireless README
2014-08-20 Added information about the 2 different sketches.
2014-09-17 S88-WirelessSlave V1.1
    Bugfixes...
2014-09-17 S88-WirelessBase V1.2
    Bugfixes and new important features...
2014-09-17 S88-WirelessSlave V1.2
    Bugfixes and new features (see BASE sketch for details).
2014-09-17 V1.2 RELEASE
    PCB version of the S88-Wireless BASE.
    The sensivity of the error checker function has been changed since it worked to fast.
2014-09-17 V1.2 RELEASE
    PCB version of the S88-Wireless Slave.
2014-09-17 README.md updated V1.2
2014-09-17 V1.2 BASE PCB
    PCB for the BASE sketch V1.2
2014-09-17 V2.0 SLAVE PCB
    PCB for the SLAVE sketch V1.2
2014-09-17 Update LICENSE
2015-08-16 Intelligent Servo Decoder V1.0
2015-08-16 Intelligent Servo Decoder V1.0
    README
2016-04-13 Create gh-pages branch via GitHub
2016-06-02 First release
2016-06-02 Stickers & schematic
2016-07-19 BUGFIX: shiftStatusLED
2017-03-02 C-rail turnout

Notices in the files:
DCCSwitchController/PCB.brd:
© Dylan Van Assche (2014)
parts and their libraries:
SparkFun-Boards: Licensing: CC v3.0 Share-Alike You are welcome to use this library for commercial purposes.
